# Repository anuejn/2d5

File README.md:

# Reverse engineering 5D mark II (5D2) image sensor

This repository contains notes and tools for reverse engineering the image sensor of the Canon EOS 5D mark II
DSLR. The reverse engineering is work in progress and not in a state where the sensor is useable.
The image sensor is relatively cheap available (~40€) and has a "full frame" sized active area
(36mm × 24mm) with 5,616px × 3,744px (21.0 MP). The 5D mark II important in popularizing DSLR cameras
for video making and the Magic Lantern firmware was originally written for this camera.

The best place to start exploring the repository is reading the files on different topics in the
[`docs/`](docs/) directory. Other folders are less easy to follow but contain raw data obtained in 
the reverse engineering process.

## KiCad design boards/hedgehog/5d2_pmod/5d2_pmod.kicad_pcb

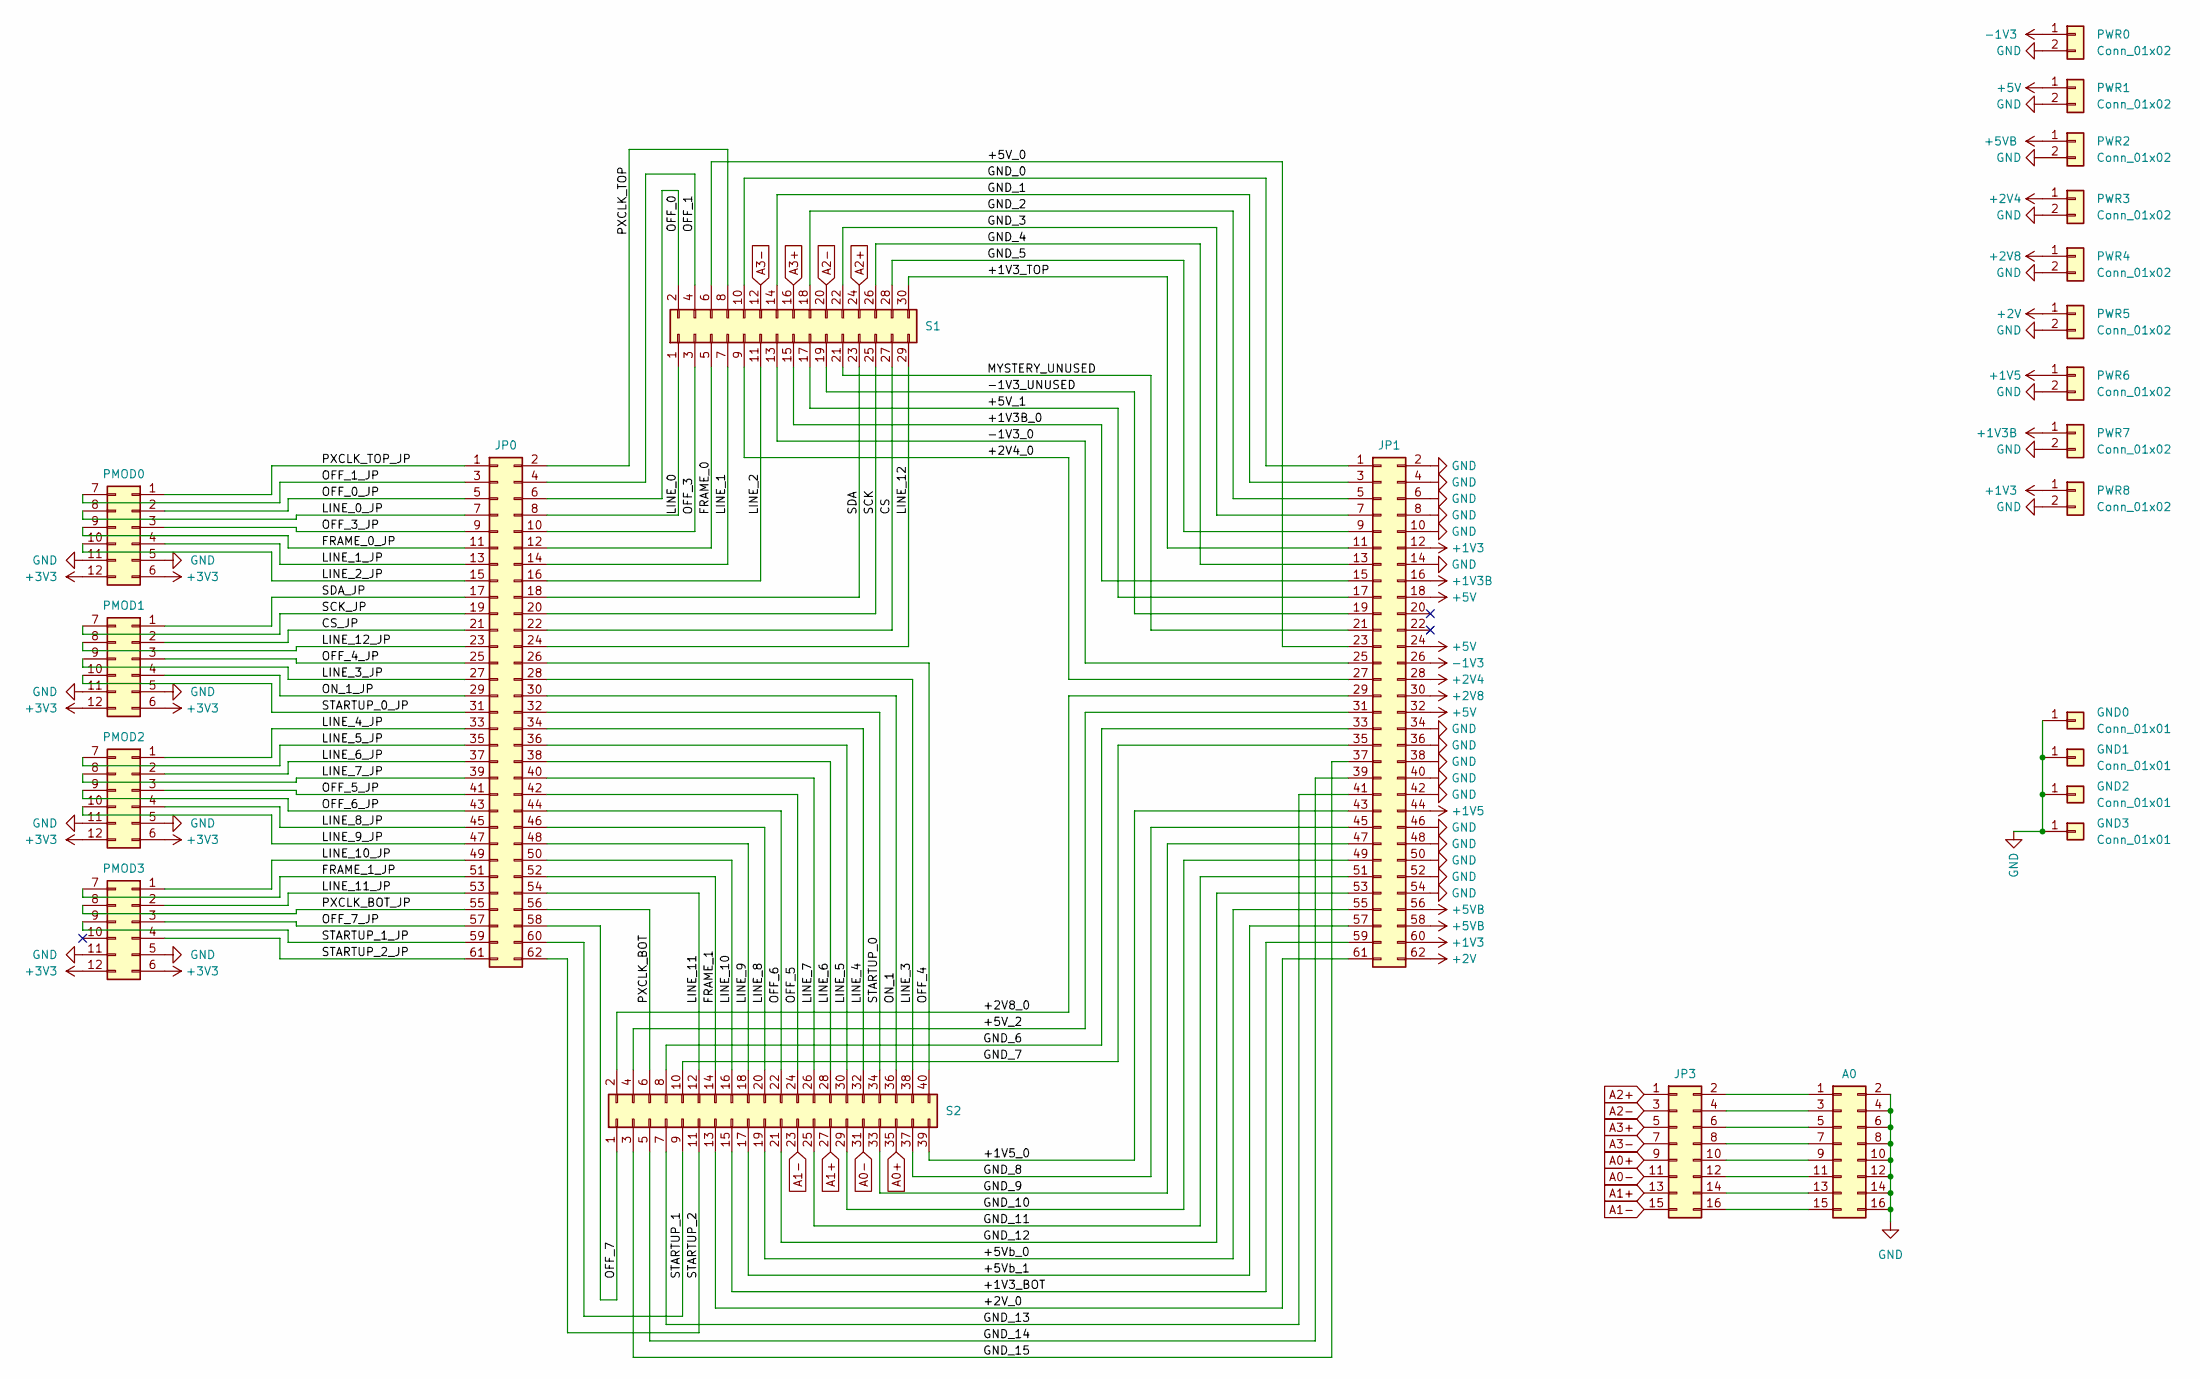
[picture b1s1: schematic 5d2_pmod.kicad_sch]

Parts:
A0: Conn_02x08_Odd_Even; PinHeader_2x08_P2.54mm_Horizontal
GND0, GND1, GND2, GND3: Conn_01x01; PinHeader_1x01_P2.54mm_Vertical
JP0, JP1: Conn_02x31_Odd_Even; PinHeader_2x31_P2.54mm_Vertical
JP3: Conn_02x08_Odd_Even; PinHeader_2x08_P2.54mm_Vertical
PMOD0, PMOD1, PMOD2, PMOD3: Conn_02x06_Top_Bottom; PMOD
PWR0, PWR1, PWR2, PWR3, PWR4, PWR5, PWR6, PWR7, PWR8: Conn_01x02; PinHeader_1x02_P2.54mm_Horizontal
S1: Conn_02x15_Odd_Even; AXK5F30
S2: Conn_02x20_Odd_Even; AXK5F40

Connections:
+1V3: JP1.12, JP1.60, PWR8.1
+1V3B: JP1.16, PWR7.1
+1V5: JP1.44, PWR6.1
+2V: JP1.62, PWR5.1
+2V4: JP1.28, PWR3.1
+2V8: JP1.30, PWR4.1
+3V3: PMOD0.6, PMOD0.12, PMOD1.6, PMOD1.12, PMOD2.6, PMOD2.12, PMOD3.6, PMOD3.12
+5V: JP1.18, JP1.24, JP1.32, PWR1.1
+5VB: JP1.56, JP1.58, PWR2.1
-1V3: JP1.26, PWR0.1
/+1V3B_0: JP1.15, S1.15
/+1V3_BOT: JP1.59, S2.15
/+1V3_TOP: JP1.11, S1.30
/+1V5_0: JP1.43, S2.39
/+2V4_0: JP1.27, S1.9
/+2V8_0: JP1.29, S2.2
/+2V_0: JP1.61, S2.13
/+5V_0: JP1.23, S1.6
/+5V_1: JP1.17, S1.17
/+5V_2: JP1.31, S2.4
/+5Vb_0: JP1.55, S2.19
/+5Vb_1: JP1.57, S2.17
/-1V3_0: JP1.25, S1.13
/-1V3_UNUSED: JP1.19, S1.19
/CS: JP0.22, S1.27
/CS_JP: JP0.21, PMOD1.2
/FRAME_0: JP0.12, S1.5
/FRAME_0_JP: JP0.11, PMOD0.9
/FRAME_1: JP0.52, S2.14
/FRAME_1_JP: JP0.51, PMOD3.7
/GND_0: JP1.1, S1.10
/GND_1: JP1.3, S1.14
/GND_2: JP1.5, S1.18
/GND_3: JP1.7, S1.22
/GND_4: JP1.13, S1.26
/GND_5: JP1.9, S1.28
/GND_6: JP1.33, S2.8
/GND_7: JP1.35, S2.10
/GND_8: JP1.45, S2.37
/GND_9: JP1.47, S2.33
/GND_10: JP1.49, S2.29
/GND_11: JP1.51, S2.25
/GND_12: JP1.53, S2.21
/GND_13: JP1.41, S2.7
/GND_14: JP1.39, S2.5
/GND_15: JP1.37, S2.3
/LINE_0: JP0.8, S1.1
/LINE_0_JP: JP0.7, PMOD0.8
/LINE_1: JP0.14, S1.7
/LINE_1_JP: JP0.13, PMOD0.4
/LINE_2: JP0.16, S1.11
/LINE_2_JP: JP0.15, PMOD0.10
/LINE_3: JP0.28, S2.38
/LINE_3_JP: JP0.27, PMOD1.9
/LINE_4: JP0.34, S2.32
/LINE_4_JP: JP0.33, PMOD2.1
/LINE_5: JP0.36, S2.30
/LINE_5_JP: JP0.35, PMOD2.7
/LINE_6: JP0.38, S2.28
/LINE_6_JP: JP0.37, PMOD2.2
/LINE_7: JP0.40, S2.26
/LINE_7_JP: JP0.39, PMOD2.8
/LINE_8: JP0.46, S2.20
/LINE_8_JP: JP0.45, PMOD2.4
/LINE_9: JP0.48, S2.18
/LINE_9_JP: JP0.47, PMOD2.10
/LINE_10: JP0.50, S2.16
/LINE_10_JP: JP0.49, PMOD3.1
/LINE_11: JP0.54, S2.12
/LINE_11_JP: JP0.53, PMOD3.2
/LINE_12: JP0.24, S1.29
/LINE_12_JP: JP0.23, PMOD1.8
/MYSTERY_UNUSED: JP1.21, S1.21
/OFF_0: JP0.6, S1.2
/OFF_0_JP: JP0.5, PMOD0.2
/OFF_1: JP0.4, S1.4
/OFF_1_JP: JP0.3, PMOD0.7
/OFF_3: JP0.10, S1.3
/OFF_3_JP: JP0.9, PMOD0.3
/OFF_4: JP0.26, S2.40
/OFF_4_JP: JP0.25, PMOD1.3
/OFF_5: JP0.42, S2.24
/OFF_5_JP: JP0.41, PMOD2.3
/OFF_6: JP0.44, S2.22
/OFF_6_JP: JP0.43, PMOD2.9
/OFF_7: JP0.58, S2.1
/OFF_7_JP: JP0.57, PMOD3.3
/ON_1: JP0.30, S2.36
/ON_1_JP: JP0.29, PMOD1.4
/PXCLK_BOT: JP0.56, S2.6
/PXCLK_BOT_JP: JP0.55, PMOD3.8
/PXCLK_TOP: JP0.2, S1.8
/PXCLK_TOP_JP: JP0.1, PMOD0.1
/SCK: JP0.20, S1.25
/SCK_JP: JP0.19, PMOD1.7
/SDA: JP0.18, S1.23
/SDA_JP: JP0.17, PMOD1.1
/STARTUP_0: JP0.32, S2.34
/STARTUP_0_JP: JP0.31, PMOD1.10
/STARTUP_1: JP0.60, S2.9
/STARTUP_1_JP: JP0.59, PMOD3.9
/STARTUP_2: JP0.62, S2.11
/STARTUP_2_JP: JP0.61, PMOD3.4
A0+: JP3.9, S2.35
A0-: JP3.11, S2.31
A1+: JP3.13, S2.27
A1-: JP3.15, S2.23
A2+: JP3.1, S1.24
A2-: JP3.3, S1.20
A3+: JP3.5, S1.16
A3-: JP3.7, S1.12
GND: A0.2, A0.4, A0.6, A0.8, A0.10, A0.12, A0.14, A0.16, GND0.1, GND1.1, GND2.1, GND3.1, JP1.2, JP1.4, JP1.6, JP1.8, JP1.10, JP1.14, JP1.34, JP1.36, JP1.38, JP1.40, JP1.42, JP1.46, JP1.48, JP1.50, JP1.52, JP1.54, PMOD0.5, PMOD0.11, PMOD1.5, PMOD1.11, PMOD2.5, PMOD2.11, PMOD3.5, PMOD3.11, PWR0.2, PWR1.2, PWR2.2, PWR3.2, PWR4.2, PWR5.2, PWR6.2, PWR7.2, PWR8.2
unnamed: A0.1, JP3.2
unnamed: A0.3, JP3.4
unnamed: A0.5, JP3.6
unnamed: A0.7, JP3.8
unnamed: A0.9, JP3.10
unnamed: A0.11, JP3.12
unnamed: A0.13, JP3.14
unnamed: A0.15, JP3.16

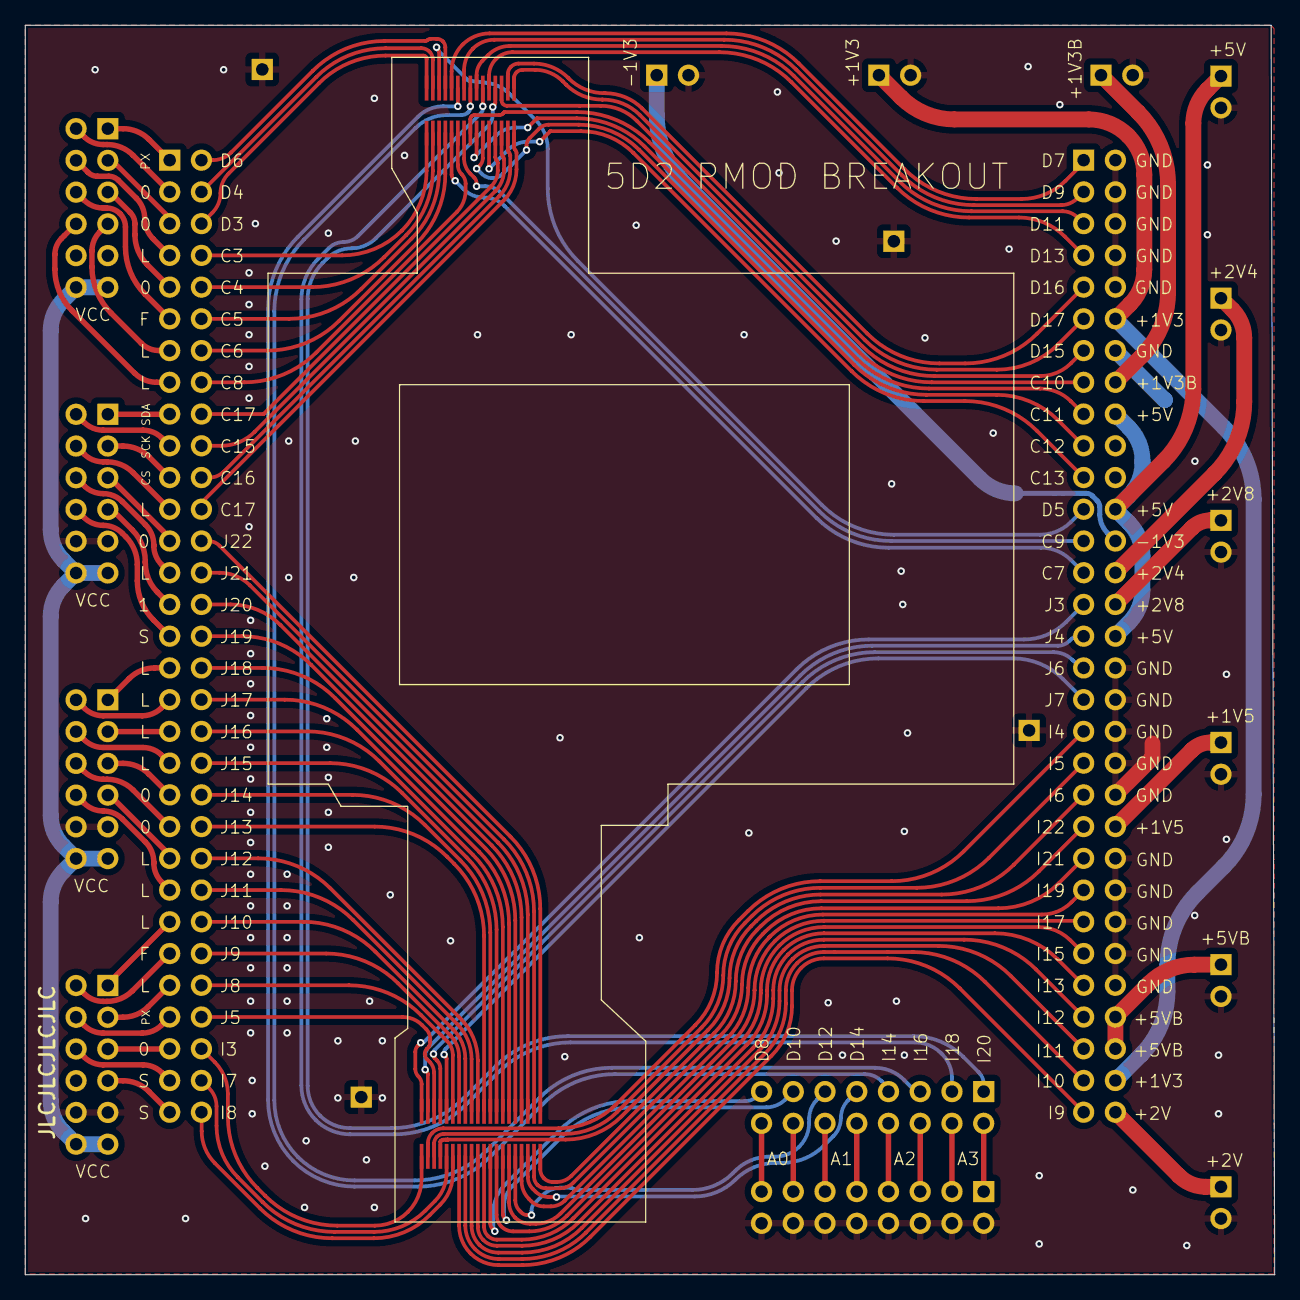
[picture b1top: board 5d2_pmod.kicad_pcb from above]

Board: 2 copper layers, 100.0 x 100.0 mm, 23 parts (0 on the bottom side), 120 nets.

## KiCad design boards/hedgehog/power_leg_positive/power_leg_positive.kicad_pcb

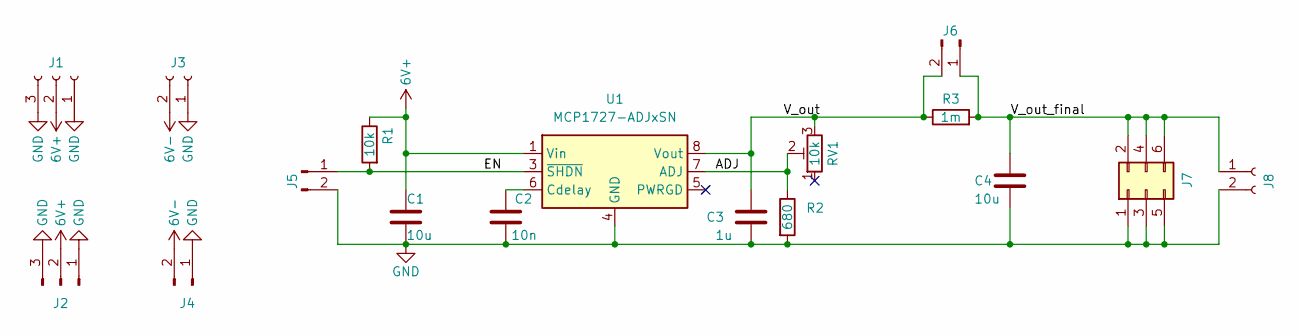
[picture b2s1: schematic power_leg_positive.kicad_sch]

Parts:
C1, C4: 10u; C_0603_1608Metric
C2: 10n; C_0603_1608Metric
C3: 1u; C_0603_1608Metric
J1: Conn_01x03_Socket; PinSocket_1x03_P2.54mm_Horizontal
J2: Conn_01x03_Pin; PinHeader_1x03_P2.54mm_Horizontal
J3, J8: Conn_01x02_Socket; PinSocket_1x02_P2.54mm_Horizontal
J4: Conn_01x02_Pin; PinHeader_1x02_P2.54mm_Horizontal
J5, J6: Conn_01x02_Pin; PinHeader_1x02_P2.54mm_Vertical
J7: Conn_02x03_Odd_Even; PinHeader_2x03_P2.54mm_Vertical
R1: 10k; R_0603_1608Metric
R2: 680; R_0603_1608Metric
R3: 1m; R_1206_3216Metric
RV1: 10k; Potentiometer_Bourns_3296W_Vertical; MPN C118963
U1: MCP1727-ADJxSN; SOIC-8_3.9x4.9mm_P1.27mm

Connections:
6V+: C1.1, J1.2, J2.2, R1.1, U1.1 (Vin), U1.2 (Vin)
6V-: J3.2, J4.2
/ADJ: R2.1, RV1.2, U1.7 (ADJ)
/EN: J5.1, R1.2, U1.3 (~SHDN)
/V_out: C3.1, J6.2, R3.1, RV1.3, U1.8 (Vout)
/V_out_final: C4.1, J6.1, J7.2, J7.4, J7.6, J8.1, R3.2
GND: C1.2, C2.1, C3.2, C4.2, J1.1, J1.3, J2.1, J2.3, J3.1, J4.1, J5.2, J7.1, J7.3, J7.5, J8.2, R2.2, U1.4 (GND)
unnamed: C2.2, U1.6 (Cdelay)

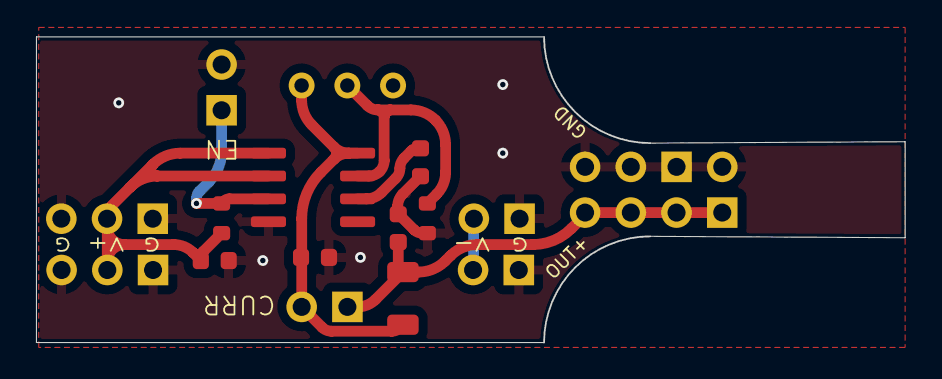
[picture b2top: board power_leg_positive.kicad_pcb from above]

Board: 2 copper layers, 48.3 x 17.0 mm, 17 parts (0 on the bottom side), 8 nets.

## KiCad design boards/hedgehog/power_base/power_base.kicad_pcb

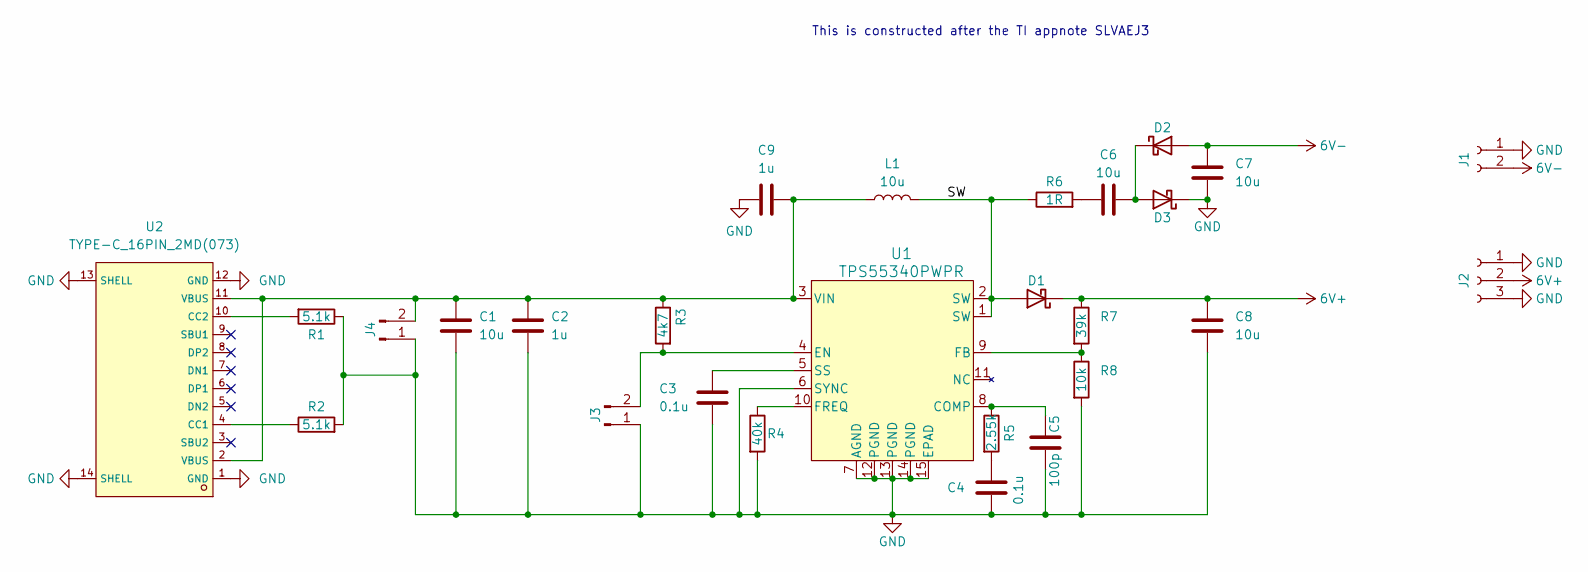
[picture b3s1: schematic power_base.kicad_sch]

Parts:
C1, C6, C7, C8: 10u; C_0603_1608Metric; LCSC C15850
C2, C9: 1u; C_0603_1608Metric; LCSC C15849
C3, C4: 0.1u; C_0603_1608Metric; LCSC C14663
C5: 100p; C_0603_1608Metric; LCSC C14858
D1, D2, D3: D_Schottky; D_SMA; MPN C8678; LCSC C8678
J1: Conn_01x02_Socket; PinSocket_1x02_P2.54mm_Horizontal
J2: Conn_01x03_Socket; PinSocket_1x03_P2.54mm_Horizontal
J3, J4: Conn_01x02_Pin; PinHeader_1x02_P2.54mm_Vertical
L1: 10u; IND-SMD_L7.3-W6.6; MPN C128692; LCSC C128692
R1, R2: 5.1k; R_0603_1608Metric; LCSC C23186
R3: 4k7; R_0603_1608Metric; LCSC C23162
R4: 40k; R_0603_1608Metric; LCSC C23153
R5: 2.55k; R_0603_1608Metric; LCSC C25965
R6: 1R; R_0805_2012Metric; LCSC C25271
R7: 39k; R_0603_1608Metric; LCSC C23153
R8: 10k; R_0603_1608Metric; LCSC C25804
U1: TPS55340PWPR; PWP14; LCSC C43862
U2: TYPE-C_16PIN_2MD(073); USB-C-SMD_TYPE-C-6PIN-2MD-073; LCSC C2765186

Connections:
6V+: C8.1, D1.1 (K), J2.2, R7.1
6V-: C7.1, D2.2 (A), J1.2
/SW: D1.2 (A), L1.2, R6.1, U1.1 (SW), U1.2 (SW)
GND: C1.2, C2.2, C3.2, C4.2, C5.2, C7.2, C8.2, C9.2, D3.1 (K), J1.1, J2.1, J2.3, J3.1, J4.1, R1.1, R2.2, R4.2, R8.2, U1.6 (SYNC), U1.7 (AGND), U1.12 (PGND), U1.13 (PGND), U1.14 (PGND), U1.15 (EPAD), U2.1 (GND), U2.12 (GND), U2.13 (SHELL), U2.14 (SHELL)
unnamed: C4.1, R5.2
unnamed: C6.1, R6.2
unnamed: C6.2, D2.1 (K), D3.2 (A)
unnamed: J3.2, R3.2, U1.4 (EN)
unnamed: C1.1, C2.1, C9.1, J4.2, L1.1, R3.1, U1.3 (VIN), U2.2 (VBUS), U2.11 (VBUS)
unnamed: C5.1, R5.1, U1.8 (COMP)
unnamed: R7.2, R8.1, U1.9 (FB)
unnamed: R4.1, U1.10 (FREQ)
unnamed: C3.1, U1.5 (SS)
unnamed: R2.1, U2.4 (CC1)
unnamed: R1.2, U2.10 (CC2)

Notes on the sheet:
This is constructed after the TI appnote SLVAEJ3

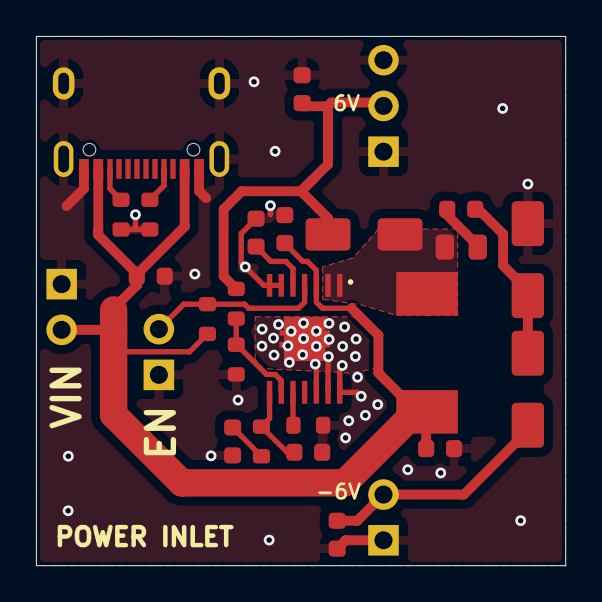
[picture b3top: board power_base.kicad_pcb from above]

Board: 2 copper layers, 29.4 x 29.4 mm, 27 parts (0 on the bottom side), 15 nets.

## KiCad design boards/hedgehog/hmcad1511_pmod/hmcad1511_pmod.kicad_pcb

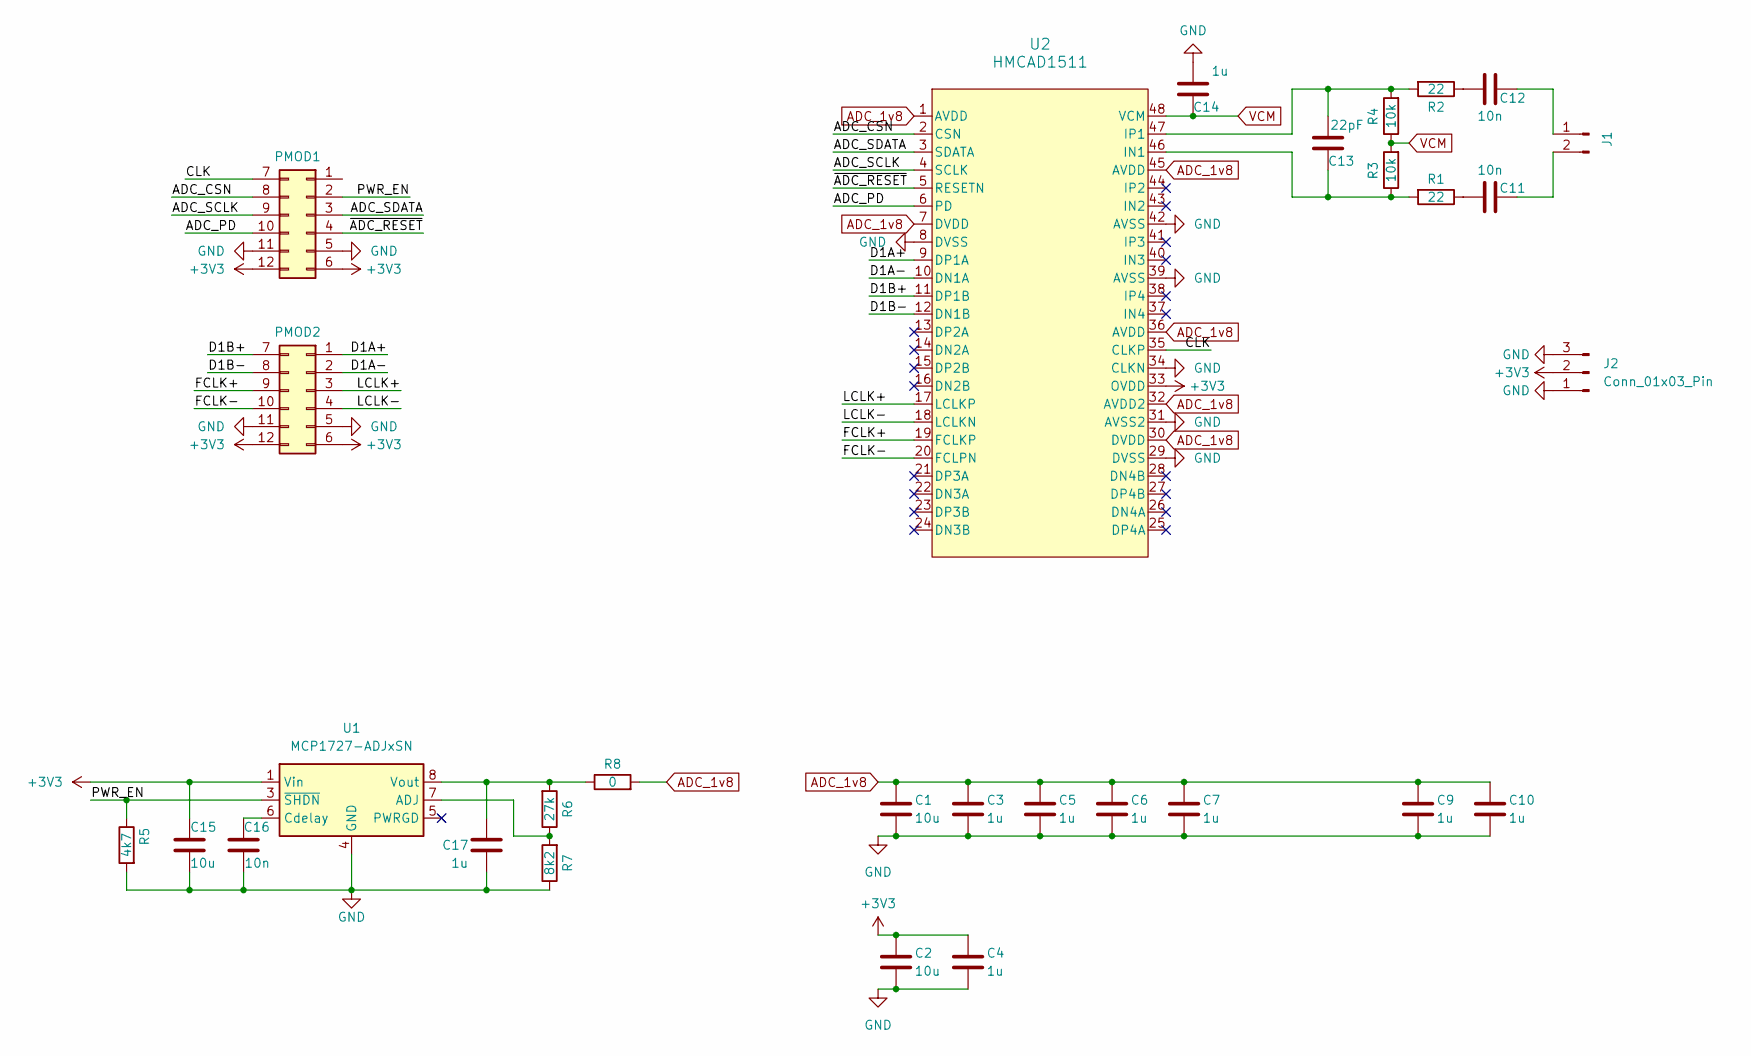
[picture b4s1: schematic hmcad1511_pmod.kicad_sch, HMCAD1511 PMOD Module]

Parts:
C1, C2, C15: 10u; C_0603_1608Metric
C3, C4, C5, C6, C7, C9, C10, C14, C17: 1u; C_0603_1608Metric
C11, C12, C16: 10n; C_0603_1608Metric
C13: 22pF; C_0603_1608Metric
J1: Conn_01x02_Pin; PinHeader_1x02_P2.54mm_Horizontal
J2: Conn_01x03_Pin; PinHeader_1x03_P2.54mm_Horizontal
PMOD1, PMOD2: Conn_02x06_Top_Bottom; PMOD
R1, R2: 22; R_0603_1608Metric
R3, R4: 10k; R_0603_1608Metric
R5: 4k7; R_0603_1608Metric
R6: 27k; C_0603_1608Metric
R7: 8k2; C_0603_1608Metric
R8: 0; C_0603_1608Metric
U1: MCP1727-ADJxSN; SOIC-8_3.9x4.9mm_P1.27mm
U2: HMCAD1511; QFN_48_ADI

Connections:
+3V3: C2.1, C4.1, C15.1, J2.2, PMOD1.6, PMOD1.12, PMOD2.6, PMOD2.12, U1.1 (Vin), U1.2 (Vin), U2.33 (OVDD)
/ADC_CSN: PMOD1.8, U2.2 (CSN)
/ADC_PD: PMOD1.10, U2.6 (PD)
/ADC_SCLK: PMOD1.9, U2.4 (SCLK)
/ADC_SDATA: PMOD1.3, U2.3 (SDATA)
/CLK: PMOD1.7, U2.35 (CLKP)
/D1A+: PMOD2.1, U2.9 (DP1A)
/D1A-: PMOD2.2, U2.10 (DN1A)
/D1B+: PMOD2.7, U2.11 (DP1B)
/D1B-: PMOD2.8, U2.12 (DN1B)
/FCLK+: PMOD2.9, U2.19 (FCLKP)
/FCLK-: PMOD2.10, U2.20 (FCLPN)
/LCLK+: PMOD2.3, U2.17 (LCLKP)
/LCLK-: PMOD2.4, U2.18 (LCLKN)
/PWR_EN: PMOD1.2, R5.1, U1.3 (~SHDN)
/~ADC_RESET: PMOD1.4, U2.5 (RESETN)
ADC_1v8: C1.1, C3.1, C5.1, C6.1, C7.1, C9.1, C10.1, R8.2, U2.1 (AVDD), U2.7 (DVDD), U2.30 (DVDD), U2.32 (AVDD2), U2.36 (AVDD), U2.45 (AVDD)
GND: C1.2, C2.2, C3.2, C4.2, C5.2, C6.2, C7.2, C9.2, C10.2, C14.2, C15.2, C16.1, C17.2, J2.1, J2.3, PMOD1.5, PMOD1.11, PMOD2.5, PMOD2.11, R5.2, R7.1, U1.4 (GND), U2.8 (DVSS), U2.29 (DVSS), U2.31 (AVSS2), U2.34 (CLKN), U2.39 (AVSS), U2.42 (AVSS)
unnamed: C11.2, R1.1
unnamed: C12.2, R2.1
unnamed: C12.1, J1.1
unnamed: C11.1, J1.2
unnamed: R6.1, R7.2, U1.7 (ADJ)
unnamed: C16.2, U1.6 (Cdelay)
unnamed: C17.1, R6.2, R8.1, U1.8 (Vout)
unnamed: C13.1, R1.2, R3.1, U2.46 (IN1)
unnamed: C13.2, R2.2, R4.2, U2.47 (IP1)
VCM: C14.1, R3.2, R4.1, U2.48 (VCM)

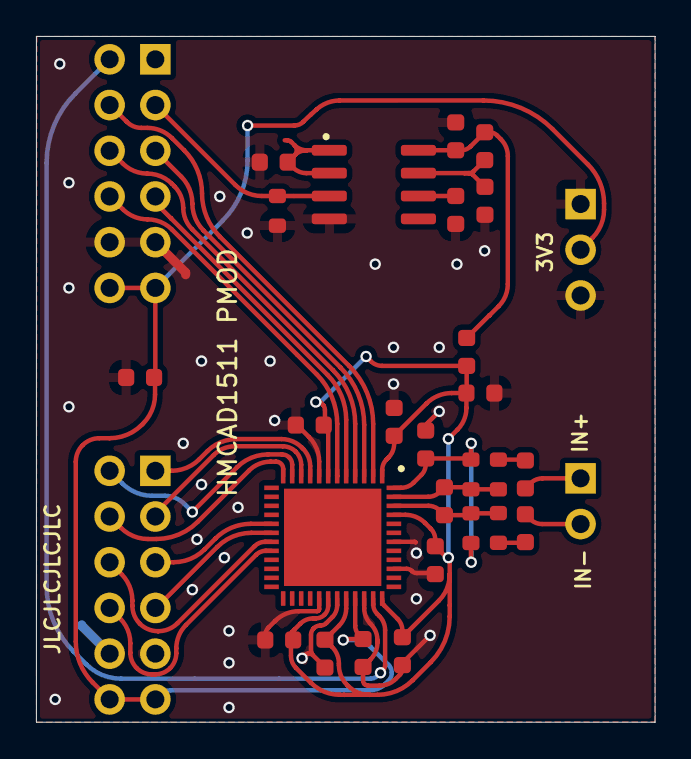
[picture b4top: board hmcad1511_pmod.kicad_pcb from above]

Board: 2 copper layers, 34.4 x 38.1 mm, 30 parts (0 on the bottom side), 28 nets.

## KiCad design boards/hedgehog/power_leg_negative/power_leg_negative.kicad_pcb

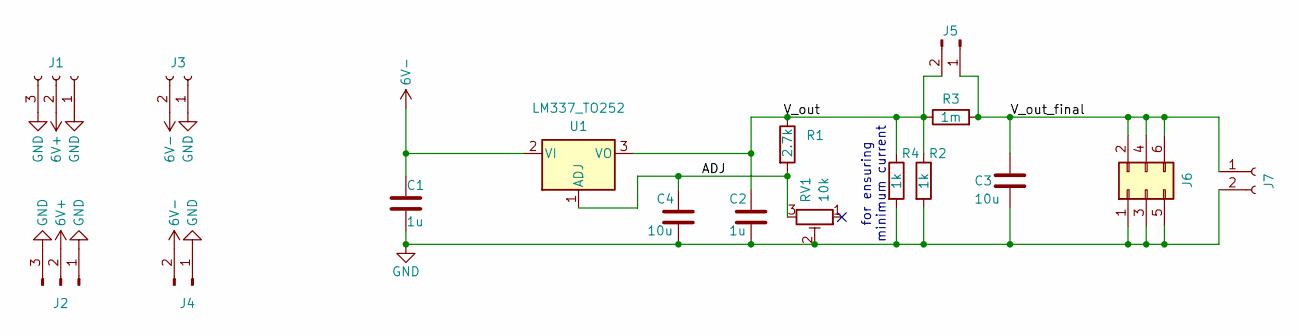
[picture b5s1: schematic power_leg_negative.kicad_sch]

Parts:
C1, C2: 1u; C_0603_1608Metric
C3, C4: 10u; C_0603_1608Metric
J1: Conn_01x03_Socket; PinSocket_1x03_P2.54mm_Horizontal
J2: Conn_01x03_Pin; PinHeader_1x03_P2.54mm_Horizontal
J3, J7: Conn_01x02_Socket; PinSocket_1x02_P2.54mm_Horizontal
J4: Conn_01x02_Pin; PinHeader_1x02_P2.54mm_Horizontal
J5: Conn_01x02_Pin; PinHeader_1x02_P2.54mm_Vertical
J6: Conn_02x03_Odd_Even; PinHeader_2x03_P2.54mm_Vertical
R1: 2.7k; R_0603_1608Metric
R2, R4: 1k; R_0603_1608Metric
R3: 1m; R_1206_3216Metric
RV1: 10k; Potentiometer_Bourns_3296W_Vertical; MPN C118963
U1: LM337_TO252; TO-252-2

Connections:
6V+: J1.2, J2.2
6V-: C1.1, J3.2, J4.2, U1.2 (VI)
/ADJ: C4.1, R1.2, RV1.3, U1.1 (ADJ)
/V_out: C2.1, J5.2, R1.1, R2.1, R3.1, R4.1, U1.3 (VO)
/V_out_final: C3.1, J5.1, J6.2, J6.4, J6.6, J7.1, R3.2
GND: C1.2, C2.2, C3.2, C4.2, J1.1, J1.3, J2.1, J2.3, J3.1, J4.1, J6.1, J6.3, J6.5, J7.2, R2.2, R4.2, RV1.2

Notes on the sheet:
for ensuring minimum current

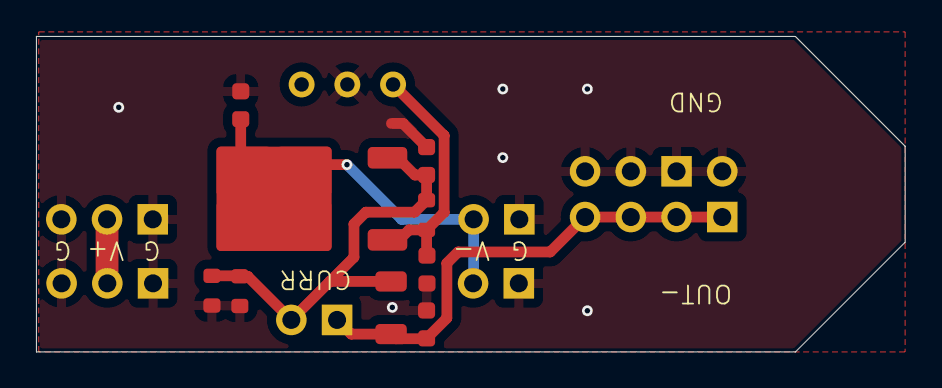
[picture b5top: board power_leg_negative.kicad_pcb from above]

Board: 2 copper layers, 48.3 x 17.5 mm, 17 parts (0 on the bottom side), 6 nets.

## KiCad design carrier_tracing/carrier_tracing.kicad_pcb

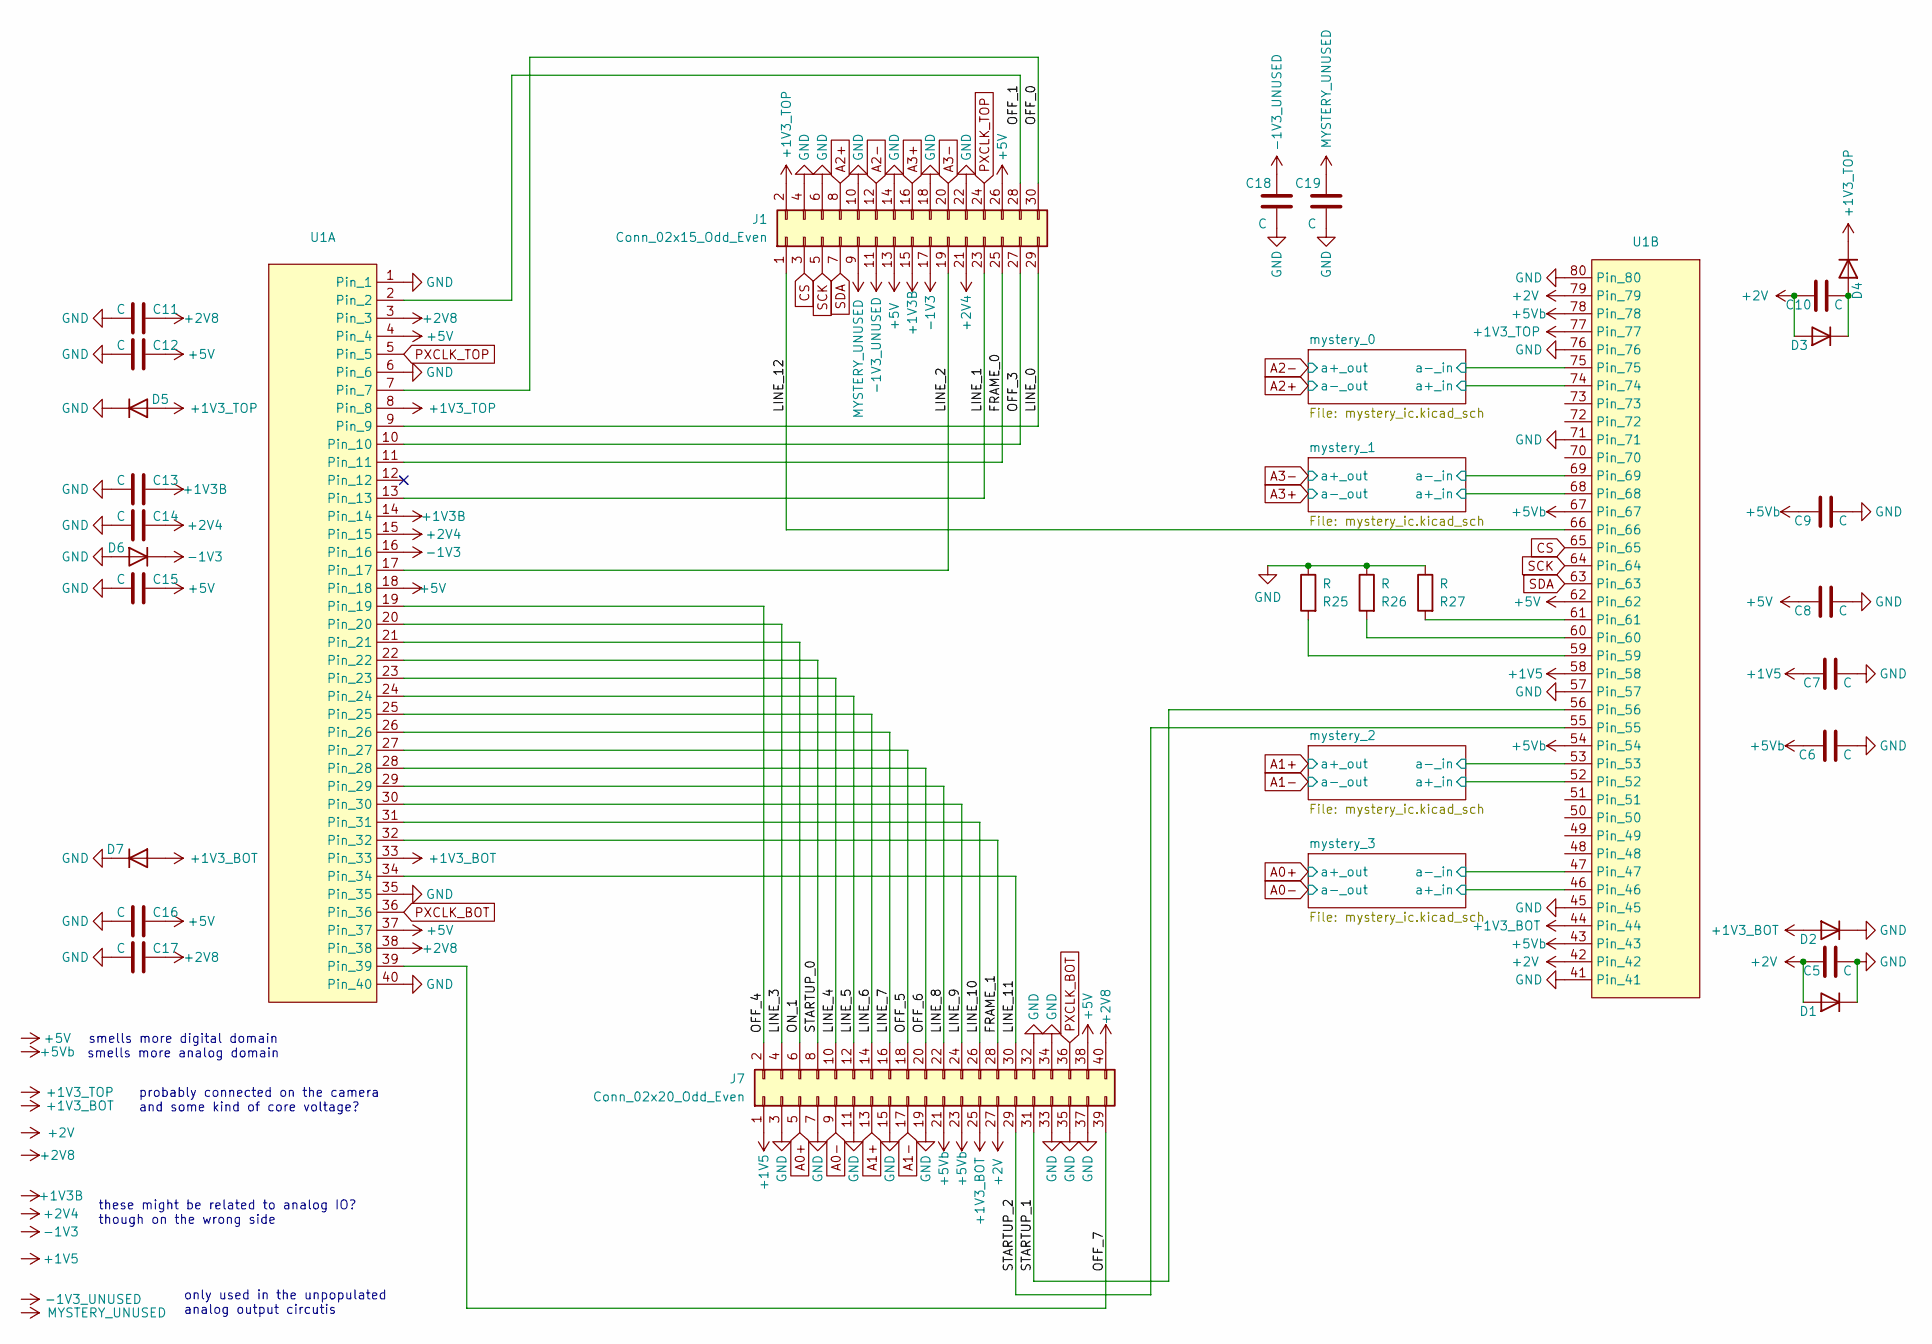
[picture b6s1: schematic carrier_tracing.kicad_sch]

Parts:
C5, C6, C7, C8, C9, C10, C11, C12, C13, C14, C15, C16, C17, C18, C19: C; C_0603_1608Metric
D1, D2, D3, D4, D5, D6, D7: D; D_0603_1608Metric
J1: Conn_02x15_Odd_Even; AXK5F30
J7: Conn_02x20_Odd_Even; AXK5F40
R25, R26, R27: R; R_0603_1608Metric
U1: 2d5

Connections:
+1V3B: C13.1, J1.15, U1.14
+1V3_BOT: D2.2 (A), D7.2 (A), J7.25, U1.33, U1.44
+1V3_TOP: D4.1 (K), D5.2 (A), J1.2, U1.8, U1.77
+1V5: C7.1, J7.1, U1.58
+2V: C5.1, C10.1, D1.2 (A), D3.2 (A), J7.27, U1.42, U1.79
+2V4: C14.1, J1.21, U1.15
+2V8: C11.1, C17.1, J7.40, U1.3, U1.38
+5V: C8.1, C12.1, C15.1, C16.1, J1.13, J1.26, J7.38, U1.4, U1.18, U1.37, U1.62
+5Vb: C6.1, C9.1, J7.21, J7.23, U1.43, U1.54, U1.67, U1.78
-1V3: D6.1 (K), J1.17, U1.16
-1V3_UNUSED: C18.1, J1.11; also elsewhere on the board
/FRAME_0: J1.25, U1.11
/FRAME_1: J7.28, U1.32
/LINE_0: J1.29, U1.9
/LINE_1: J1.23, U1.13
/LINE_2: J1.19, U1.17
/LINE_3: J7.4, U1.20
/LINE_4: J7.10, U1.23
/LINE_5: J7.12, U1.24
/LINE_6: J7.14, U1.25
/LINE_7: J7.16, U1.26
/LINE_8: J7.22, U1.29
/LINE_9: J7.24, U1.30
/LINE_10: J7.26, U1.31
/LINE_11: J7.30, U1.34
/LINE_12: J1.1, U1.66
/OFF_0: J1.30, U1.7
/OFF_1: J1.28, U1.2
/OFF_3: J1.27, U1.10
/OFF_4: J7.2, U1.19
/OFF_5: J7.18, U1.27
/OFF_6: J7.20, U1.28
/OFF_7: J7.39, U1.39
/ON_1: J7.6, U1.21
/STARTUP_0: J7.8, U1.22
/STARTUP_1: J7.31, U1.56
/STARTUP_2: J7.29, U1.55
/mystery_0/a+_in: U1.74; also elsewhere on the board
/mystery_0/a-_in: U1.75; also elsewhere on the board
/mystery_1/a+_in: U1.68; also elsewhere on the board
/mystery_1/a-_in: U1.69; also elsewhere on the board
/mystery_2/a+_in: U1.52; also elsewhere on the board
/mystery_2/a-_in: U1.53; also elsewhere on the board
/mystery_3/a+_in: U1.46; also elsewhere on the board
/mystery_3/a-_in: U1.47; also elsewhere on the board
A0+: J7.5; also elsewhere on the board
A0-: J7.9; also elsewhere on the board
A1+: J7.13; also elsewhere on the board
A1-: J7.17; also elsewhere on the board
A2+: J1.8; also elsewhere on the board
A2-: J1.12; also elsewhere on the board
A3+: J1.16; also elsewhere on the board
A3-: J1.20; also elsewhere on the board
CS: J1.3, U1.65
GND: C5.2, C6.2, C7.2, C8.2, C9.2, C11.2, C12.2, C13.2, C14.2, C15.2, C16.2, C17.2, C18.2, C19.2, D1.1 (K), D2.1 (K), D5.1 (K), D6.2 (A), D7.1 (K), J1.4, J1.6, J1.10, J1.14, J1.18, J1.22, J7.3, J7.7, J7.11, J7.15, J7.19, J7.32, J7.33, J7.34, J7.35, J7.37, R25.1, R26.1, R27.1, U1.1, U1.6, U1.35, U1.40, U1.41, U1.45, U1.57, U1.71, U1.76, U1.80
MYSTERY_UNUSED: C19.1, J1.9; also elsewhere on the board
unnamed: C10.2, D3.1 (K), D4.2 (A)
unnamed: R25.2, U1.59
unnamed: R26.2, U1.60
unnamed: R27.2, U1.61
PXCLK_BOT: J7.36, U1.36
PXCLK_TOP: J1.24, U1.5
SCK: J1.5, U1.64
SDA: J1.7, U1.63

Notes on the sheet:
only used in the unpopulated analog output circutis
these might be related to analog IO? though on the wrong side
smells more digital domain smells more analog domain
probably connected on the camera and some kind of core voltage?

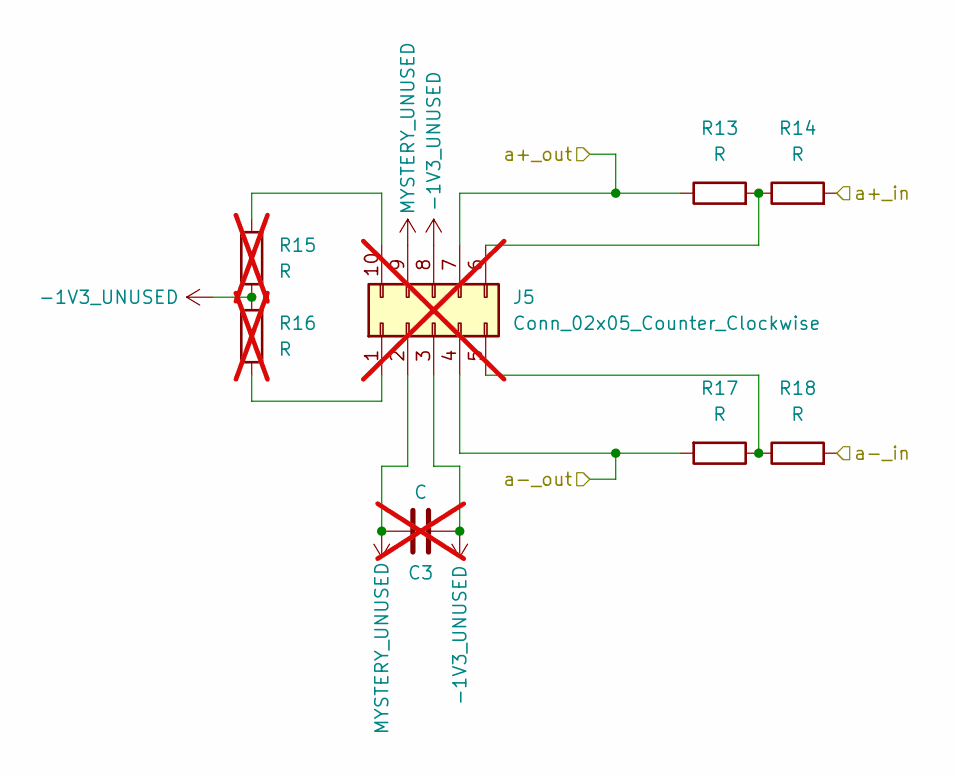
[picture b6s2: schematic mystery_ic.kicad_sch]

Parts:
C3: C; R_0603_1608Metric; not fitted
J5: Conn_02x05_Counter_Clockwise; SOIC-10; not fitted
R13, R14, R17, R18: R; R_0603_1608Metric
R15, R16: R; R_0603_1608Metric; not fitted

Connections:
-1V3_UNUSED: C3.2, J5.3, J5.8, R15.2, R16.1; also elsewhere on the board
/mystery_1/a+_in: R14.2; also elsewhere on the board
/mystery_1/a-_in: R18.2; also elsewhere on the board
A3+: J5.4, R17.2; also elsewhere on the board
A3-: J5.7, R13.1; also elsewhere on the board
MYSTERY_UNUSED: C3.1, J5.2, J5.9; also elsewhere on the board
unnamed: J5.1, R16.2
unnamed: J5.5, R17.1, R18.1
unnamed: J5.6, R13.2, R14.1
unnamed: J5.10, R15.1

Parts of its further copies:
C1, C2, C4: C; R_0603_1608Metric; not fitted
J3, J4, J6: Conn_02x05_Counter_Clockwise; SOIC-10; not fitted
R1, R2, R5, R6, R7, R8, R11, R12, R21, R22, R23, R24: R; R_0603_1608Metric
R3, R4, R9, R10, R19, R20: R; R_0603_1608Metric; not fitted

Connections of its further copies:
-1V3_UNUSED: C1.2, C2.2, C4.2, J3.3, J3.8, J4.3, J4.8, J6.3, J6.8, R3.2, R4.1, R9.2, R10.1, R19.2, R20.1; also elsewhere on the board
/mystery_0/a+_in: R23.2; also elsewhere on the board
/mystery_0/a-_in: R24.2; also elsewhere on the board
/mystery_2/a+_in: R2.2; also elsewhere on the board
/mystery_2/a-_in: R6.2; also elsewhere on the board
/mystery_3/a+_in: R8.2; also elsewhere on the board
/mystery_3/a-_in: R12.2; also elsewhere on the board
A0+: J4.7, R7.1; also elsewhere on the board
A0-: J4.4, R11.2; also elsewhere on the board
A1+: J3.7, R1.1; also elsewhere on the board
A1-: J3.4, R5.2; also elsewhere on the board
A2+: J6.4, R22.2; also elsewhere on the board
A2-: J6.7, R21.1; also elsewhere on the board
MYSTERY_UNUSED: C1.1, C2.1, C4.1, J3.2, J3.9, J4.2, J4.9, J6.2, J6.9; also elsewhere on the board
unnamed: J3.1, R4.2
unnamed: J3.5, R5.1, R6.1
unnamed: J3.6, R1.2, R2.1
unnamed: J3.10, R3.1
unnamed: J4.1, R10.2
unnamed: J4.5, R11.1, R12.1
unnamed: J4.6, R7.2, R8.1
unnamed: J4.10, R9.1
unnamed: J6.1, R20.2
unnamed: J6.5, R22.1, R24.1
unnamed: J6.6, R21.2, R23.1
unnamed: J6.10, R19.1
